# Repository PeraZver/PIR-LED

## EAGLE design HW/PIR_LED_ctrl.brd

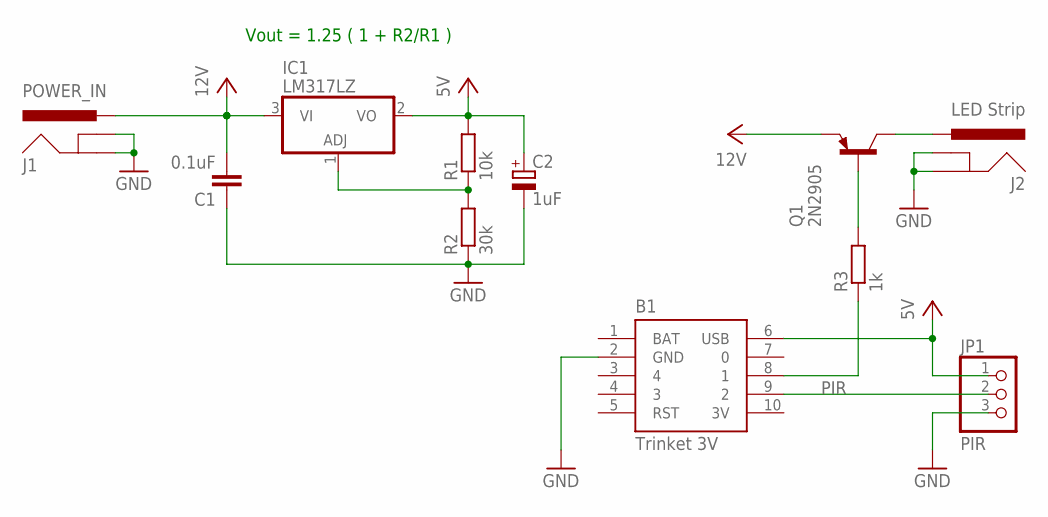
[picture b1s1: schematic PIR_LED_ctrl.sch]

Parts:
B1: Trinket 3V; TRINKET_3V
C1: 0.1uF; C025-025X050
C2: 1uF; E5-6
IC1: LM317LZ; TO92
J1: POWER_IN; POWER_JACK_PTH
J2: LED Strip; POWER_JACK_PTH
JP1: PIR; 1X03_ROUND
Q1: 2N2905; TO39
R1: 10k; 0207/10
R2: 30k; 0207/10
R3: 1k; 0207/10

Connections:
5V: B1.6 (USB), C2.+, IC1.2 (VO), JP1.1, R1.2
12V: C1.2, IC1.3 (VI), J1.PWR, Q1.1 (E)
GND: B1.2 (GND), C1.1, C2.-, J1.GND, J1.GNDBREAK, J2.GND, J2.GNDBREAK, JP1.3, R2.1
unnamed: IC1.1 (ADJ), R1.1, R2.2
unnamed: J2.PWR, Q1.3 (C)
unnamed: B1.8 (1), R3.1
unnamed: Q1.2 (B), R3.2
PIR: B1.9 (2), JP1.2

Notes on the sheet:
Vout = 1.25 ( 1 + R2/R1 )

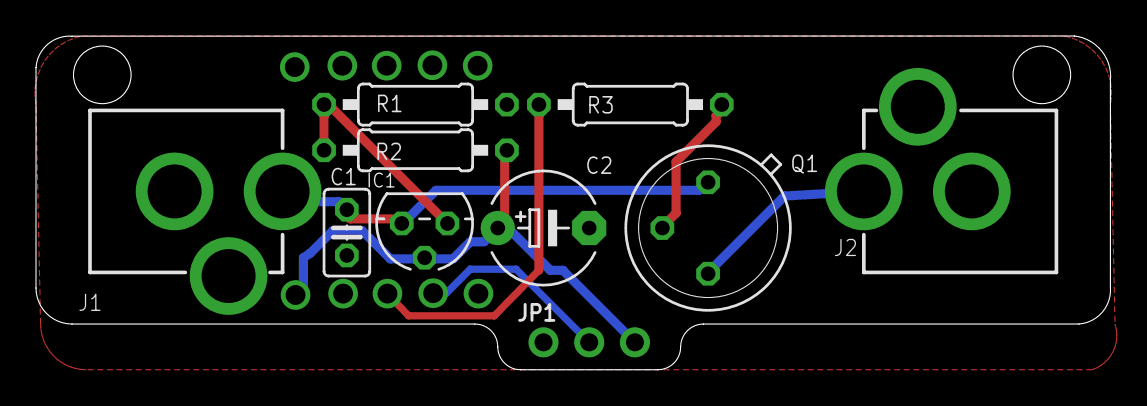
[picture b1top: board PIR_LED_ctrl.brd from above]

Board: 2 copper layers, 59.7 x 18.5 mm, 12 parts (1 on the bottom side), 8 nets.

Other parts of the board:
U$1: A5L-LOC

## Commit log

2017-02-08 started sch
2017-02-08 added brd file
2017-02-17 added holes and released everything
2017-02-26 3D finished
2017-08-19 introduced WS2812 led strip

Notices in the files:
parts and their libraries:
SparkFun-Connectors: Licensing: Creative Commons ShareAlike 4.0 International - https://creativecommons.org/licenses/by-sa/4.0
microbuilder: This work is placed in the public domain, and may be freely used for commercial and non-commercial work with the following conditions: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
